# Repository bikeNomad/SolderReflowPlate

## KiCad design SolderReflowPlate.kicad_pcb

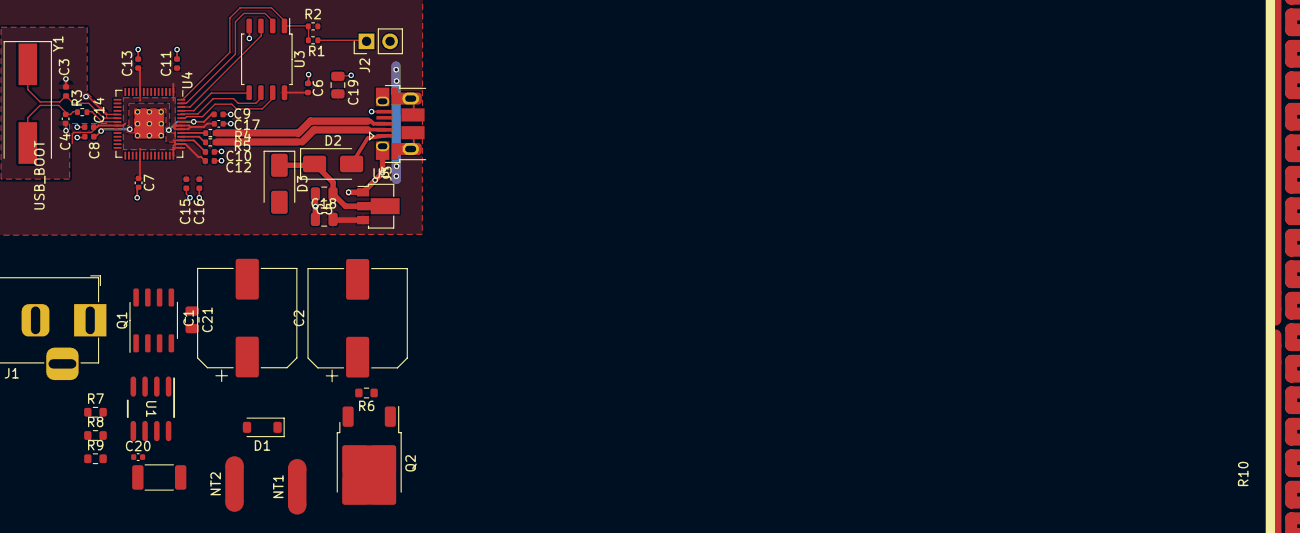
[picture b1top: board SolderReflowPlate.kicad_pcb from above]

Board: 2 copper layers, 48 parts (0 on the bottom side), 25 nets.

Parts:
C1, C2: 680uF 35V; CP_Elec_10x10.5
C3, C4: 27p; C_0402_1005Metric
C5, C18, C19, C21: 10u; C_0805_2012Metric
C6, C7, C8, C9, C11, C13, C14, C15, C16, C17, C20: 100n; C_0402_1005Metric
C10, C12: 1u; C_0402_1005Metric
D1: SS54; D_SOD-123
D2, D3: SS54; D_SMA
J1: Barrel_Jack_Switch; BarrelJack_Horizontal
J2: Conn_01x02; PinHeader_1x02_P2.54mm_Vertical
J3: USB_B_Micro; USB_Micro-B_Amphenol_10103594-0001LF_Horizontal_modified
NT1, NT2#2: NetTie_2; NetTie-2_SMD_Pad2.0mm
NT1#2, NT2: NetTie_2; NetTie-2_SMD_Pad1.3mm
Q1: FDS4141-NL-VB; SOIC-8_3.9x4.9mm_P1.27mm
Q2: IRLR8726TRPBF; TO-252-2
R1, R3: 1k; R_0402_1005Metric
R2: DNF; R_0402_1005Metric
R4, R5: 27; R_0402_1005Metric
R6, R9: 10k; R_0603_1608Metric
R7, R8: 47; R_0603_1608Metric
R10: R030; R_2010_5025Metric
U1: INA219AIDR; D0008A_N
U3: W25Q128JVS; SOIC-8_5.23x5.23mm_P1.27mm
U4: RP2040; RP2040-QFN-56
U5: HT7533-1; SOT-89-3
Y1: HCM4912000000ABJT; Crystal_SMD_HC49-SD

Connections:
+1V1: C8.1, C9.1, C10.1, U4.23 (DVDD), U4.45 (VREG_VOUT), U4.50 (DVDD)
+3V3: C6.1, C7.1, C11.1, C12.1, C13.1, C14.1, C15.1, C16.1, C17.1, C18.1, C19.1, C20.1, R2.1, U1.5 (VS), U3.8 (VCC), U4.1 (IOVDD), U4.10 (IOVDD), U4.22 (IOVDD), U4.33 (IOVDD), U4.42 (IOVDD), U4.43 (ADC_AVDD), U4.44 (VREG_IN), U4.48 (USB_VDD), U4.49 (IOVDD), U5.3 (VOUT)
/CPU/QSPI_SCLK: U3.6 (CLK), U4.52 (QSPI_SCLK)
/CPU/QSPI_SD0: U3.5 (DI(IO0)), U4.53 (QSPI_SD0)
/CPU/QSPI_SD1: U3.2 (DO(IO1)), U4.55 (QSPI_SD1)
/CPU/QSPI_SD2: U3.3 (IO2), U4.54 (QSPI_SD2)
/CPU/QSPI_SD3: U3.7 (IO3), U4.51 (QSPI_SD3)
/CPU/QSPI_SS: R1.1, R2.2, U3.1 (~CS), U4.56 (QSPI_SS)
/CPU/XIN: C3.1, U4.20 (XIN), Y1.1
/CPU/XOUT: R3.1, U4.21 (XOUT)
/CPU/~USB_BOOT: J2.1, R1.2
/POWER/FET_PWM: Q2.1 (G), R6.1
GND: C1.2, C2.2, C3.2, C4.2, C5.2, C6.2, C7.2, C8.2, C9.2, C10.2, C11.2, C12.2, C13.2, C14.2, C15.2, C16.2, C17.2, C18.2, C19.2, C20.2, J1.2, J2.2, J3.5 (GND), J3.6 (Shield), Q2.3 (S), R6.2, R9.2, U1.1 (A1), U1.2 (A0), U1.6 (GND), U3.4 (GND), U4.19 (TESTEN), U4.57 (GND), U5.1 (GND)
HEATPLATE: NT1.2, NT1#2.2, NT2.2, NT2#2.2
unnamed: C4.1, R3.2, Y1.2
unnamed: D1.2 (A), NT2#2.1, Q2.2 (D)
unnamed: D1.1 (K), NT1.1, R10.2, U1.7 (IN-)
unnamed: C5.1, D2.1 (K), D3.1 (K), U5.2 (VIN)
unnamed: C21.1, D3.2 (A), J1.1, Q1.5 (D), Q1.6 (D), Q1.7 (D), Q1.8 (D), R7.2
unnamed: J1.3, R7.1, R8.1
unnamed: C21.2, Q1.4 (G), R9.1
unnamed: C1.1, C2.1, Q1.1 (S), Q1.2 (S), Q1.3 (S), R8.2, R10.1, U1.8 (IN+)
unnamed: R5.2, U4.46 (USB_DM)
unnamed: R4.2, U4.47 (USB_DP)
VBUS: D2.2 (A), J3.1 (VBUS)

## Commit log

2023-05-13 initial commit.
2023-05-14 Got Rpi layout together; added JLCPCB info
2023-05-14 WIP: added LCSC part numbers
2023-05-15 WIP: cleaned up top 3V3 pour
